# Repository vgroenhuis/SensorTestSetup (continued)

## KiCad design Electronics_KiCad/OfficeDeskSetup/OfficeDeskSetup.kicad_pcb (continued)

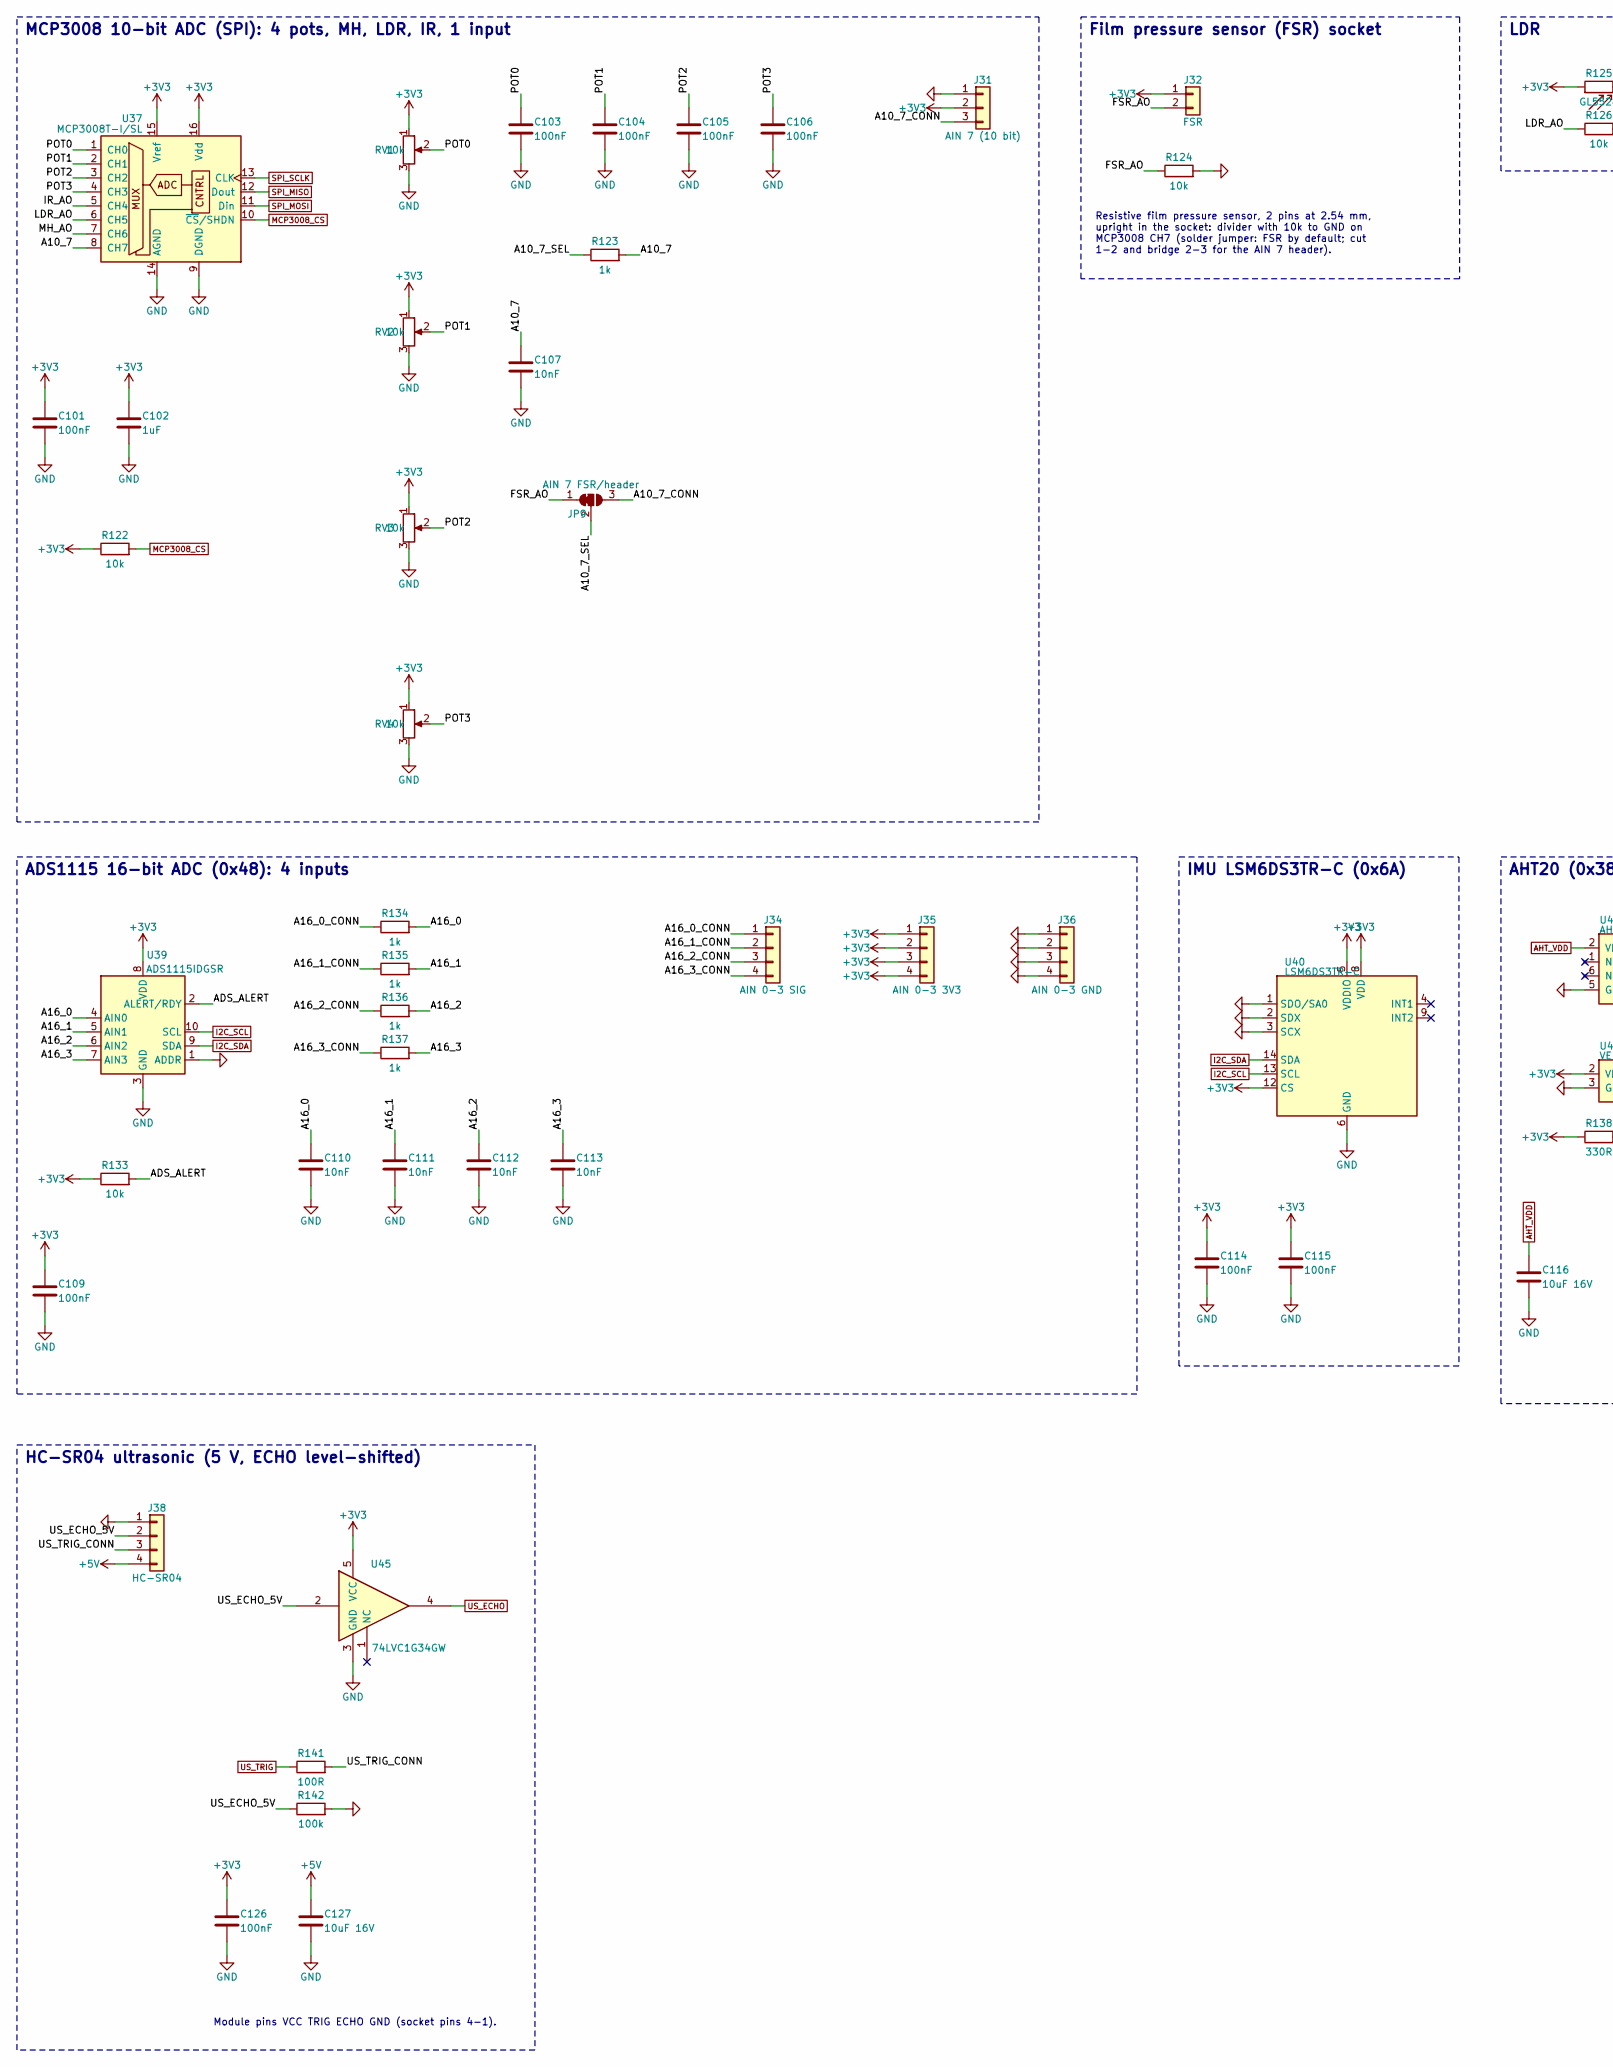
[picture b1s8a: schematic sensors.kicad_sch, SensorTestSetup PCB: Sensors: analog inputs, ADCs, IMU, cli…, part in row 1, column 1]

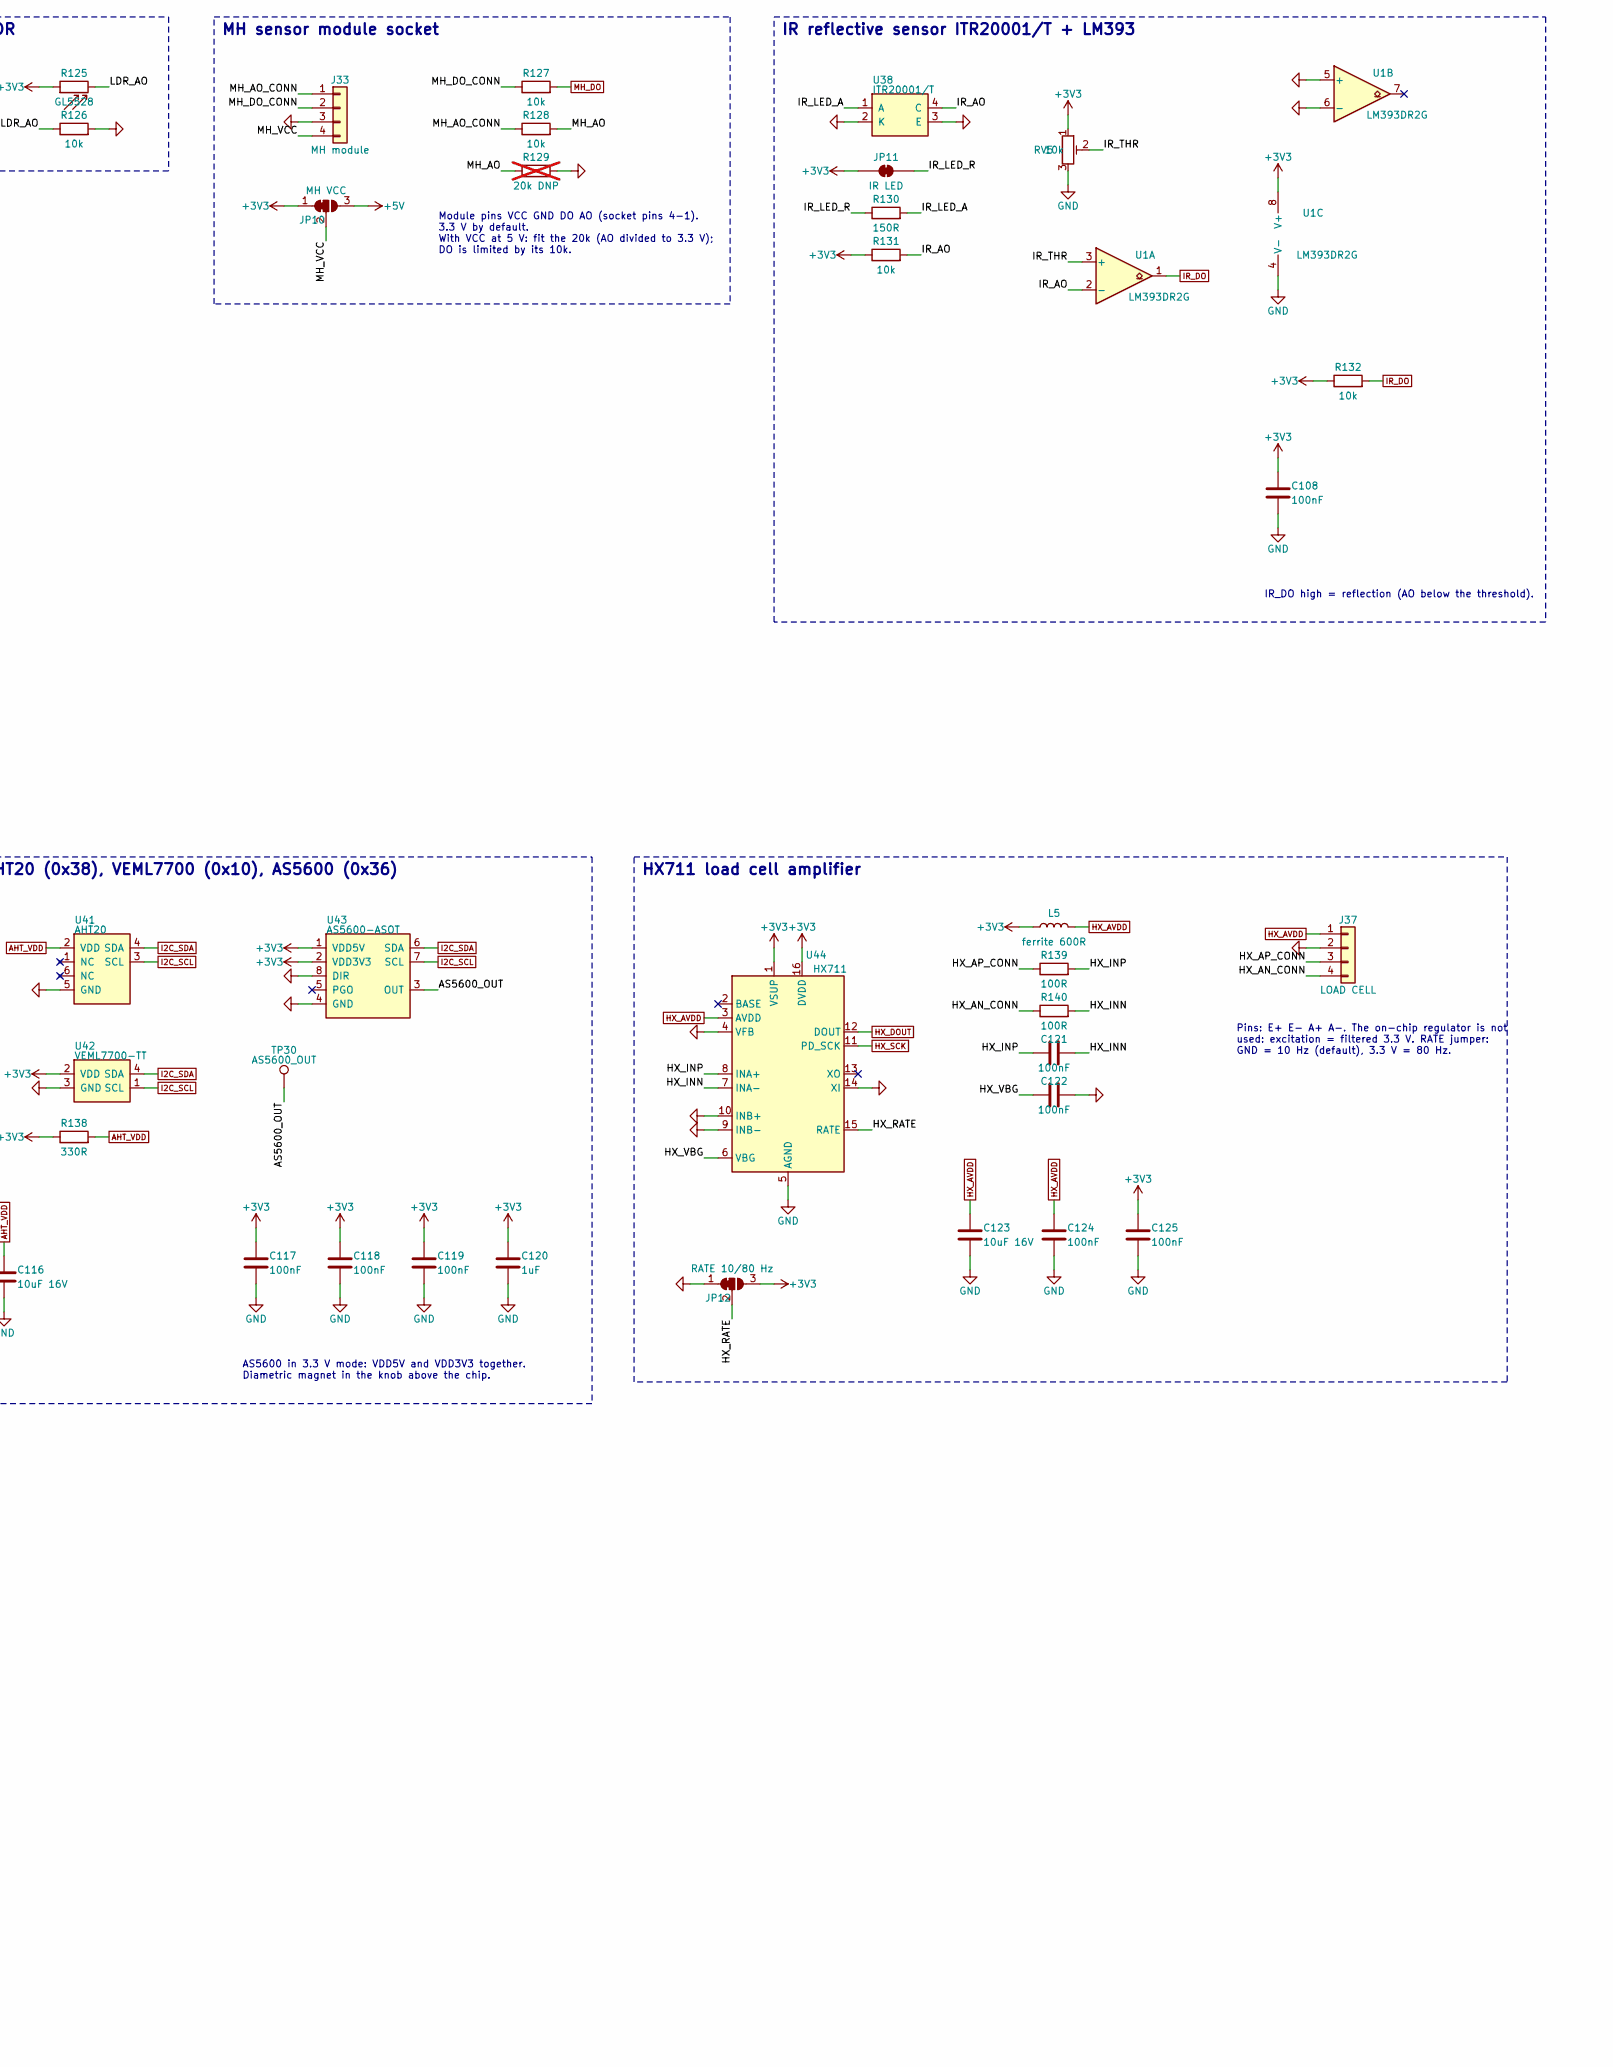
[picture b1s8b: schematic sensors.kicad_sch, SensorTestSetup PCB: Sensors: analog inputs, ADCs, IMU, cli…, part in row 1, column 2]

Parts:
C101, C103, C104, C105, C106, C108, C109, C114, C115, C117, C118, C119, C121, C122, C124, C125, C126: 100nF; C_0603_1608Metric; LCSC C14663
C102, C120: 1uF; C_0603_1608Metric; LCSC C15849
C107, C110, C111, C112, C113: 10nF; C_0603_1608Metric; LCSC C57112
C116, C123, C127: 10uF 16V; C_0805_2012Metric; LCSC C15850
J31: AIN 7 (10 bit); PinHeader_1x03_P2.54mm_Vertical; LCSC C49257
J32: FSR; PinSocket_1x02_P2.54mm_Vertical
J33: MH module; PinSocket_1x04_P2.54mm_Vertical; LCSC C2718488
J34: AIN 0-3 SIG; PinHeader_1x04_P2.54mm_Vertical; LCSC C42431808
J35: AIN 0-3 3V3; PinHeader_1x04_P2.54mm_Vertical; LCSC C42431808
J36: AIN 0-3 GND; PinHeader_1x04_P2.54mm_Vertical; LCSC C42431808
J37: LOAD CELL; JST_PH_B4B-PH-K_1x04_P2.00mm_Vertical; LCSC C131334
J38: HC-SR04; PinSocket_1x04_P2.54mm_Vertical; LCSC C2718488
JP9: AIN 7 FSR/header; SolderJumper-3_P1.3mm_Bridged12_RoundedPad1.0x1.5mm
JP10: MH VCC; SolderJumper-3_P1.3mm_Bridged12_RoundedPad1.0x1.5mm
JP11: IR LED; SolderJumper-2_P1.3mm_Bridged_RoundedPad1.0x1.5mm
JP12: RATE 10/80 Hz; SolderJumper-3_P1.3mm_Bridged12_RoundedPad1.0x1.5mm
L5: ferrite 600R; R_0603_1608Metric; LCSC C1002
R122, R124, R126, R127, R128, R131, R132, R133: 10k; R_0603_1608Metric; LCSC C25804
R123, R134, R135, R136, R137: 1k; R_0603_1608Metric; LCSC C21190
R125: GL5528; R_LDR_5.1x4.3mm_P3.4mm_Vertical; LCSC C125627
R129: 20k DNP; R_0603_1608Metric; LCSC C4184; not fitted
R130: 150R; R_0603_1608Metric; LCSC C22808
R138: 330R; R_0603_1608Metric; LCSC C23138
R139, R140, R141: 100R; R_0603_1608Metric; LCSC C22775
R142: 100k; R_0603_1608Metric; LCSC C25803
RV1, RV2, RV3, RV4: 10k; Potentiometer_Alps_RK09K_Single_Vertical; LCSC C209770
RV5: 10k; Potentiometer_Bourns_3314G_Vertical; LCSC C780220
TP30: AS5600_OUT; TestPoint_Pad_D1.5mm
U1: LM393DR2G; SOIC-8_3.9x4.9mm_P1.27mm; LCSC C7955
U37: MCP3008T-I/SL; SOIC-16_3.9x9.9mm_P1.27mm; LCSC C2651321
U38: ITR20001/T; OPTO-TH_4P_ITR20001-T-F316; LCSC C264269
U39: ADS1115IDGSR; TSSOP-10_3x3mm_P0.5mm; LCSC C37593
U40: LSM6DS3TR-C; LGA-14_3x2.5mm_P0.5mm_LayoutBorder3x4y; LCSC C967633
U41: AHT20; SENSOR-SMD_L3.0-W3.0-P1.00-BR; LCSC C2757850
U42: VEML7700-TT; SENSOR-SMD_EML7700-TT; LCSC C1850416
U43: AS5600-ASOT; SOIC-8_3.9x4.9mm_P1.27mm; LCSC C55240803
U44: HX711; SOIC-16_3.9x9.9mm_P1.27mm; LCSC C6705483
U45: 74LVC1G34GW; SOT-353_SC-70-5; LCSC C52140426

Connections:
+3V3: C101.1, C102.1, C108.1, C109.1, C114.1, C115.1, C117.1, C118.1, C119.1, C120.1, C125.1, C126.1, J31.2, J32.1, J35.1, J35.2, J35.3, J35.4, JP10.1 (A), JP11.1 (A), JP12.3 (B), L5.1, R122.1, R125.1, R131.1, R132.1, R133.1, R138.1, RV1.1, RV2.1, RV3.1, RV4.1, RV5.1, U1.8 (V+), U37.15 (Vref), U37.16 (Vdd), U39.8 (VDD), U40.5 (VDDIO), U40.8 (VDD), U40.12 (CS), U42.2 (VDD), U43.1 (VDD5V), U43.2 (VDD3V3), U44.1 (VSUP), U44.16 (DVDD), U45.5 (VCC); also elsewhere on the board
+5V: C127.1, J38.4, JP10.3 (B); also elsewhere on the board
/7 Sensors: analog inputs, ADCs, IMU, climate, light, angle, load cell, ultraso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: C107.1, R123.2, U37.8 (CH7)
/7 Sensors: analog inputs, ADCs, IMU, climate, light, angle, load cell, ultraso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: J31.3, JP9.3 (B)
/7 Sensors: analog inputs, ADCs, IMU, climate, light, angle, load cell, ultraso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: JP9.2 (C), R123.1
/7 Sensors: analog inputs, ADCs, IMU, climate, light, angle, load cell, ultraso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: C110.1, R134.2, U39.4 (AIN0)
/7 Sensors: analog inputs, ADCs, IMU, climate, light, angle, load cell, ultraso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: J34.1, R134.1
/7 Sensors: analog inputs, ADCs, IMU, climate, light, angle, load cell, ultraso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: C111.1, R135.2, U39.5 (AIN1)
/7 Sensors: analog inputs, ADCs, IMU, climate, light, angle, load cell, ultraso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: J34.2, R135.1
/7 Sensors: analog inputs, ADCs, IMU, climate, light, angle, load cell, ultraso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: C112.1, R136.2, U39.6 (AIN2)
/7 Sensors: analog inputs, ADCs, IMU, climate, light, angle, load cell, ultraso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: J34.3, R136.1
/7 Sensors: analog inputs, ADCs, IMU, climate, light, angle, load cell, ultraso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: C113.1, R137.2, U39.7 (AIN3)
/7 Sensors: analog inputs, ADCs, IMU, climate, light, angle, load cell, ultraso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: J34.4, R137.1
/7 Sensors: analog inputs, ADCs, IMU, climate, light, angle, load cell, ultraso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: R133.2, U39.2 (ALERT/RDY)
/7 Sensors: analog inputs, ADCs, IMU, climate, light, angle, load cell, ultraso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: TP30.1, U43.3 (OUT)
/7 Sensors: analog inputs, ADCs, IMU, climate, light, angle, load cell, ultraso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: J32.2, JP9.1 (A), R124.1
/7 Sensors: analog inputs, ADCs, IMU, climate, light, angle, load cell, ultraso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: J37.4, R140.1
/7 Sensors: analog inputs, ADCs, IMU, climate, light, angle, load cell, ultraso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: J37.3, R139.1
/7 Sensors: analog inputs, ADCs, IMU, climate, light, angle, load cell, ultraso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: C121.2, R140.2, U44.7 (INA-)
/7 Sensors: analog inputs, ADCs, IMU, climate, light, angle, load cell, ultraso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: C121.1, R139.2, U44.8 (INA+)
/7 Sensors: analog inputs, ADCs, IMU, climate, light, angle, load cell, ultraso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: JP12.2 (C), U44.15 (RATE)
/7 Sensors: analog inputs, ADCs, IMU, climate, light, angle, load cell, ultraso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: C122.1, U44.6 (VBG)
/7 Sensors: analog inputs, ADCs, IMU, climate, light, angle, load cell, ultraso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: R131.2, U1.2 (-), U37.5 (CH4), U38.4 (C)
/7 Sensors: analog inputs, ADCs, IMU, climate, light, angle, load cell, ultraso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: R130.2, U38.1 (A)
/7 Sensors: analog inputs, ADCs, IMU, climate, light, angle, load cell, ultraso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: JP11.2 (B), R130.1
/7 Sensors: analog inputs, ADCs, IMU, climate, light, angle, load cell, ultraso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: RV5.2, U1.3 (+)
/7 Sensors: analog inputs, ADCs, IMU, climate, light, angle, load cell, ultraso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: R125.2, R126.1, U37.6 (CH5)
/7 Sensors: analog inputs, ADCs, IMU, climate, light, angle, load cell, ultraso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: R128.2, R129.1, U37.7 (CH6)
/7 Sensors: analog inputs, ADCs, IMU, climate, light, angle, load cell, ultraso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: J33.1, R128.1
/7 Sensors: analog inputs, ADCs, IMU, climate, light, angle, load cell, ultraso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: J33.2, R127.1
/7 Sensors: analog inputs, ADCs, IMU, climate, light, angle, load cell, ultraso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: J33.4, JP10.2 (C)
/7 Sensors: analog inputs, ADCs, IMU, climate, light, angle, load cell, ultraso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: C103.1, RV1.2, U37.1 (CH0)
/7 Sensors: analog inputs, ADCs, IMU, climate, light, angle, load cell, ultraso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: C104.1, RV2.2, U37.2 (CH1)
/7 Sensors: analog inputs, ADCs, IMU, climate, light, angle, load cell, ultraso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: C105.1, RV3.2, U37.3 (CH2)
/7 Sensors: analog inputs, ADCs, IMU, climate, light, angle, load cell, ultraso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: C106.1, RV4.2, U37.4 (CH3)
/7 Sensors: analog inputs, ADCs, IMU, climate, light, angle, load cell, ultraso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: J38.2, R142.1, U45.2
/7 Sensors: analog inputs, ADCs, IMU, climate, light, angle, load cell, ultraso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: J38.3, R141.2
AHT_VDD: C116.1, R138.2, U41.2 (VDD)
GND: C101.2, C102.2, C103.2, C104.2, C105.2, C106.2, C107.2, C108.2, C109.2, C110.2, C111.2, C112.2, C113.2, C114.2, C115.2, C116.2, C117.2, C118.2, C119.2, C120.2, C122.2, C123.2, C124.2, C125.2, C126.2, C127.2, J31.1, J33.3, J36.1, J36.2, J36.3, J36.4, J37.2, J38.1, JP12.1 (A), R124.2, R126.2, R129.2, R142.2, RV1.3, RV2.3, RV3.3, RV4.3, RV5.3, U1.4 (V-), U1.5 (+), U1.6 (-), U37.9 (DGND), U37.14 (AGND), U38.2 (K), U38.3 (E), U39.1 (ADDR), U39.3 (GND), U40.1 (SDO/SA0), U40.2 (SDX), U40.3 (SCX), U40.6 (GND), U40.7 (GND), U41.5 (GND), U42.3 (GND), U43.4 (GND), U43.8 (DIR), U44.4 (VFB), U44.5 (AGND), U44.9 (INB-), U44.10 (INB+), U44.14 (XI), U45.3 (GND); also elsewhere on the board
HX_AVDD: C123.1, C124.1, J37.1, L5.2, U44.3 (AVDD)
HX_DOUT: U44.12 (DOUT); also elsewhere on the board
HX_SCK: U44.11 (PD_SCK); also elsewhere on the board
I2C_SCL: U39.10 (SCL), U40.13 (SCL), U41.3 (SCL), U42.1 (SCL), U43.7 (SCL); also elsewhere on the board
I2C_SDA: U39.9 (SDA), U40.14 (SDA), U41.4 (SDA), U42.4 (SDA), U43.6 (SDA); also elsewhere on the board
IR_DO: R132.2, U1.1; also elsewhere on the board
MCP3008_CS: R122.2, U37.10 (~CS/SHDN); also elsewhere on the board
MH_DO: R127.2; also elsewhere on the board
SPI_MISO: U37.12 (Dout); also elsewhere on the board
SPI_MOSI: U37.11 (Din); also elsewhere on the board
SPI_SCLK: U37.13 (CLK); also elsewhere on the board
US_ECHO: U45.4; also elsewhere on the board
US_TRIG: R141.1; also elsewhere on the board

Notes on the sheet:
MCP3008 10-bit ADC (SPI): 4 pots, MH, LDR, IR, 1 input
Resistive film pressure sensor, 2 pins at 2.54 mm, upright in the socket: divider with 10k to GND on MCP3008 CH7 (solder jumper: FSR by default; cut 1-2 and bridge 2-3 for the AIN 7 header).
Film pressure sensor (FSR) socket
LDR
Module pins VCC GND DO AO (socket pins 4-1). 3.3 V by default. With VCC at 5 V: fit the 20k (AO divided to 3.3 V); DO is limited by its 10k.
MH sensor module socket
IR_DO high = reflection (AO below the threshold).
IR reflective sensor ITR20001/T + LM393
ADS1115 16-bit ADC (0x48): 4 inputs
IMU LSM6DS3TR-C (0x6A)
AS5600 in 3.3 V mode: VDD5V and VDD3V3 together. Diametric magnet in the knob above the chip.
AHT20 (0x38), VEML7700 (0x10), AS5600 (0x36)
Pins: E+ E- A+ A-. The on-chip regulator is not used: excitation = filtered 3.3 V. RATE jumper: GND = 10 Hz (default), 3.3 V = 80 Hz.
HX711 load cell amplifier
Module pins VCC TRIG ECHO GND (socket pins 4-1).
HC-SR04 ultrasonic (5 V, ECHO level-shifted)

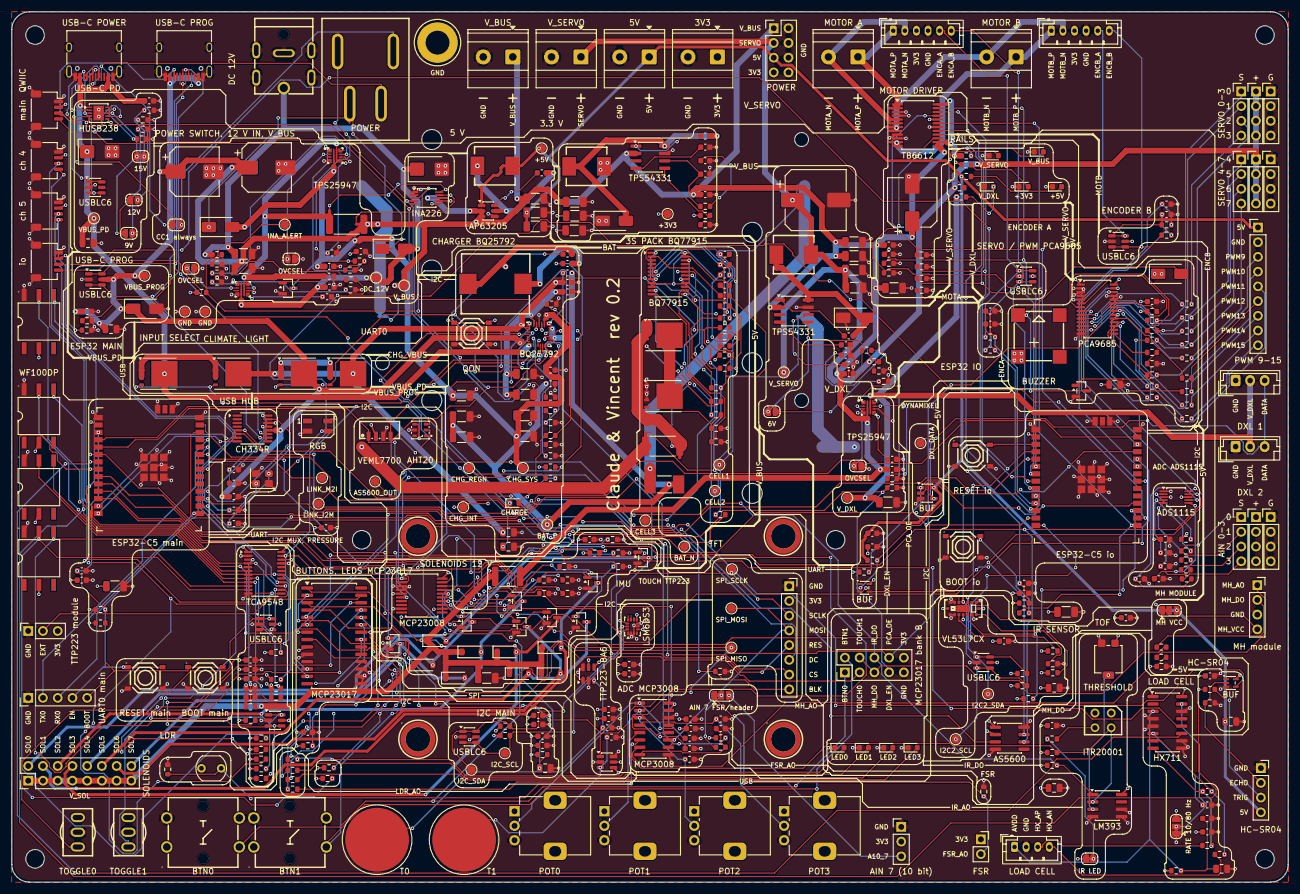
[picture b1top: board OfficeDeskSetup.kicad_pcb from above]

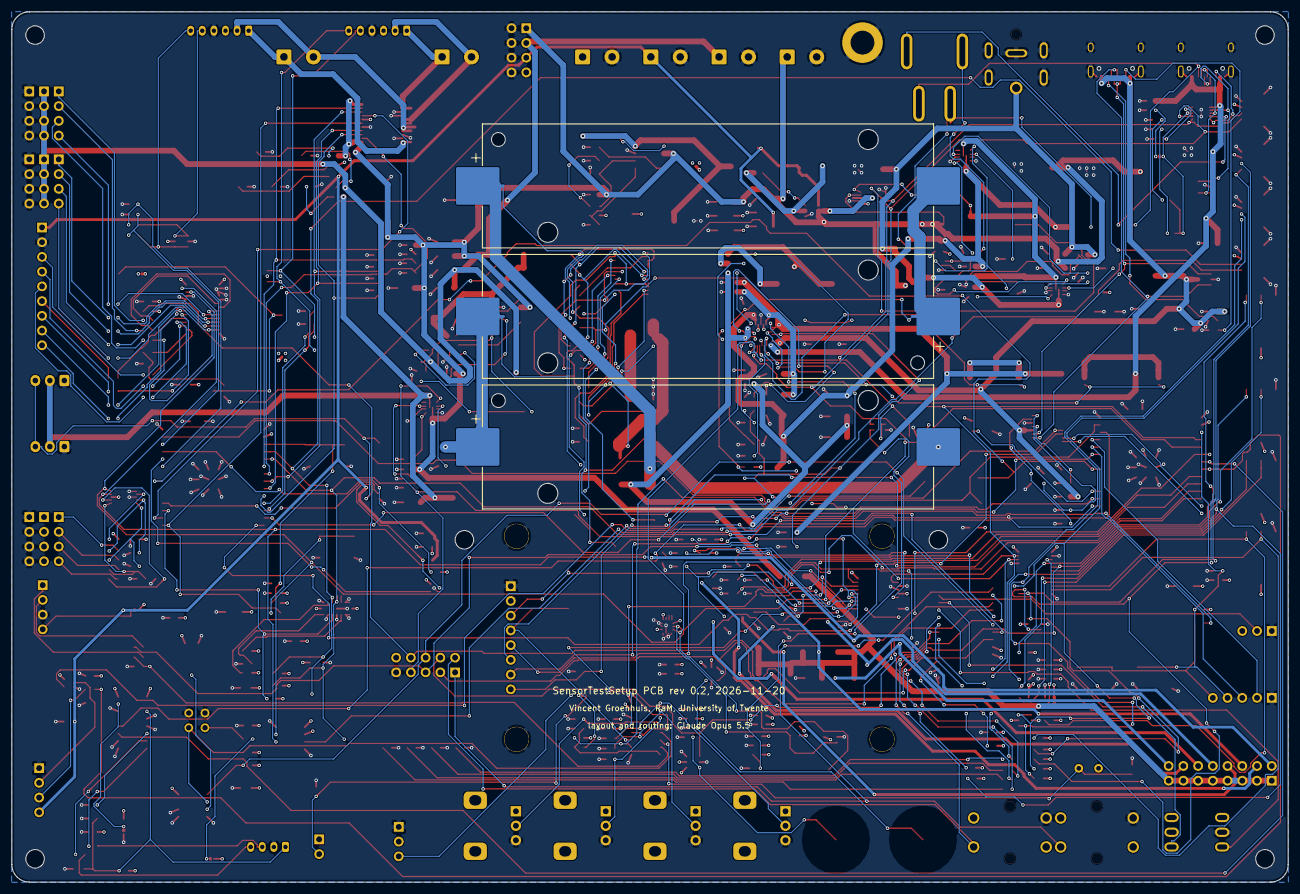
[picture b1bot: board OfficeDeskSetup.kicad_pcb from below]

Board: 4 copper layers, 220.0 x 150.0 mm, 486 parts (6 on the bottom side), 291 nets.

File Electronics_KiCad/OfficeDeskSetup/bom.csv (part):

Reference,Value,Footprint,LCSC,DNP,Sheet,Note
J1,USB-C POWER,Connector_USB:USB_C_Receptacle_HRO_TYPE-C-31-M-12,C165948,,usb_pd,
U2,HUSB238_002DD,Package_DFN_QFN:WDFN-10-1EP_3x3mm_P0.5mm_EP1.8x2.5mm,C7471904,,usb_pd,
U3,USBLC6-2SC6,Package_TO_SOT_SMD:SOT-23-6,C2827654,,usb_pd,
JP1,15V,Jumper:SolderJumper-2_P1.3mm_Bridged_RoundedPad1.0x1.5mm,,,usb_pd,
R1,14k,Resistor_SMD:R_0603_1608Metric,C22803,,usb_pd,
JP2,12V,Jumper:SolderJumper-2_P1.3mm_Open_RoundedPad1.0x1.5mm,,,usb_pd,
R2,10k,Resistor_SMD:R_0603_1608Metric,C25804,,usb_pd,
JP3,9V,Jumper:SolderJumper-2_P1.3mm_Open_RoundedPad1.0x1.5mm,,,usb_pd,
R3,6.04k,Resistor_SMD:R_0603_1608Metric,C25977,,usb_pd,
R4,ISET DNP,Resistor_SMD:R_0603_1608Metric,,DNP,usb_pd,
D1,SMBJ22A,Diode_SMD:D_SMB,C10214,,usb_pd,
C1,1uF 35V,Capacitor_SMD:C_0805_2012Metric,C28323,,usb_pd,
C2,100nF 50V,Capacitor_SMD:C_0603_1608Metric,C14663,,usb_pd,
TP1,VBUS_PD,TestPoint:TestPoint_Pad_D1.5mm,,,usb_pd,
J2,USB-C PROG,Connector_USB:USB_C_Receptacle_HRO_TYPE-C-31-M-12,C165948,,usb_pd,
R5,5.1k,Resistor_SMD:R_0603_1608Metric,C23186,,usb_pd,
R6,5.1k,Resistor_SMD:R_0603_1608Metric,C23186,,usb_pd,
D2,SMAJ5.0A,Diode_SMD:D_SMA,C19077523,,usb_pd,
U4,USBLC6-2SC6,Package_TO_SOT_SMD:SOT-23-6,C2827654,,usb_pd,
C3,10uF 16V,Capacitor_SMD:C_0805_2012Metric,C15850,,usb_pd,
C4,100nF,Capacitor_SMD:C_0603_1608Metric,C14663,,usb_pd,
TP2,VBUS_PROG,TestPoint:TestPoint_Pad_D1.5mm,,,usb_pd,
U5,CH334R,Package_SO:QSOP-16_3.9x4.9mm_P0.635mm,C4154405,,usb_pd,
Y1,12MHz,Crystal:Crystal_SMD_3225-4Pin_3.2x2.5mm,C9002,,usb_pd,
C5,100nF,Capacitor_SMD:C_0603_1608Metric,C14663,,usb_pd,
C6,1uF,Capacitor_SMD:C_0603_1608Metric,C15849,,usb_pd,
C7,100nF,Capacitor_SMD:C_0603_1608Metric,C14663,,usb_pd,
C8,15pF DNP,Capacitor_SMD:C_0603_1608Metric,C1644,DNP,usb_pd,
C9,15pF DNP,Capacitor_SMD:C_0603_1608Metric,C1644,DNP,usb_pd,
Q1,BSC0902NSI,Package_TO_SOT_SMD:TDSON-8-1,C534382,,battery,ACFET1: drain to the input
Q2,BSC0902NSI,Package_TO_SOT_SMD:TDSON-8-1,C534382,,battery,RBFET1: drain to the charger VBUS
Q3,BSC0902NSI,Package_TO_SOT_SMD:TDSON-8-1,C534382,,battery,ACFET2: drain to the input
Q4,BSC0902NSI,Package_TO_SOT_SMD:TDSON-8-1,C534382,,battery,RBFET2: drain to the charger VBUS
U6,BQ25792RQMR,Package_DFN_QFN:Texas_RQM0029A_VQFN-29_4x4mm_P0.4mm,C2862876,,battery,
L1,2.2uH 10A,OfficeDeskSetup:IND-SMD_L11.5-W10.5,C167228,,battery,
C10,47nF 50V,Capacitor_SMD:C_0603_1608Metric,C1622,,battery,
C11,47nF 50V,Capacitor_SMD:C_0603_1608Metric,C1622,,battery,
C12,1nF 50V,Capacitor_SMD:C_0603_1608Metric,C1588,,battery,
R7,13.7k,Resistor_SMD:R_0603_1608Metric,C22793,,battery,
R8,47k,Resistor_SMD:R_0603_1608Metric,C25819,,battery,
R9,100k,Resistor_SMD:R_0603_1608Metric,C25803,,battery,
R10,5.23k,Resistor_SMD:R_0603_1608Metric,C23068,,battery,
R11,30.1k,Resistor_SMD:R_0603_1608Metric,C23000,,battery,
TH1,10k B3435,Resistor_SMD:R_0603_1608Metric,C525660,,battery,
R12,10k,Resistor_SMD:R_0603_1608Metric,C25804,,battery,
R13,10k,Resistor_SMD:R_0603_1608Metric,C25804,,battery,
R14,2.2k,Resistor_SMD:R_0603_1608Metric,C4190,,battery,
D3,CHARGE yellow,LED_SMD:LED_0603_1608Metric,C2287,,battery,
SW1,QON,OfficeDeskSetup:SW-SMD_4P-L5.1-W5.1-P3.70-LS6.5-TL_H1.5,C318884,,battery,
C13,4.7uF 35V,Capacitor_SMD:C_0805_2012Metric,C76651,,battery,
C14,100nF 50V,Capacitor_SMD:C_0603_1608Metric,C14663,,battery,
C15,10uF 35V,Capacitor_SMD:C_1206_3216Metric,C13585,,battery,
C16,10uF 35V,Capacitor_SMD:C_1206_3216Metric,C13585,,battery,
C17,100nF 50V,Capacitor_SMD:C_0603_1608Metric,C14663,,battery,
C18,4.7uF 16V,Capacitor_SMD:C_0805_2012Metric,C1779,,battery,
C19,22uF 25V,Capacitor_SMD:C_1206_3216Metric,C12891,,battery,
C20,22uF 25V,Capacitor_SMD:C_1206_3216Metric,C12891,,battery,
C21,22uF 25V,Capacitor_SMD:C_1206_3216Metric,C12891,,battery,
C22,100nF 50V,Capacitor_SMD:C_0603_1608Metric,C14663,,battery,
C23,10uF 25V,Capacitor_SMD:C_1206_3216Metric,C13585,,battery,
C24,10uF 25V,Capacitor_SMD:C_1206_3216Metric,C13585,,battery,
C25,100nF 50V,Capacitor_SMD:C_0603_1608Metric,C14663,,battery,
TP3,CHG_SYS,TestPoint:TestPoint_Pad_D1.5mm,,,battery,
TP4,BAT_P,TestPoint:TestPoint_Pad_D1.5mm,,,battery,
TP5,CHG_INT,TestPoint:TestPoint_Pad_D1.5mm,,,battery,
TP6,CHG_REGN,TestPoint:TestPoint_Pad_D1.5mm,,,battery,
BT1,18650,Battery:BatteryHolder_Keystone_1042_1x18650,C2979183,,battery,holder MY-18650-01: footprint to check
BT2,18650,Battery:BatteryHolder_Keystone_1042_1x18650,C2979183,,battery,holder MY-18650-01: footprint to check
BT3,18650,Battery:BatteryHolder_Keystone_1042_1x18650,C2979183,,battery,holder MY-18650-01: footprint to check
F1,10A,Fuse:Fuse_Littelfuse-NANO2-451_453,C44479,,battery,
NT1,CELL1 tap,NetTie:NetTie-2_SMD_Pad0.5mm,,,battery,
NT2,CELL2 tap,NetTie:NetTie-2_SMD_Pad0.5mm,,,battery,
NT3,CELL3 tap,NetTie:NetTie-2_SMD_Pad0.5mm,,,battery,
NT4,Kelvin BAT-,NetTie:NetTie-2_SMD_Pad0.5mm,,,battery,
NT5,Kelvin SRN,NetTie:NetTie-2_SMD_Pad0.5mm,,,battery,
U7,BQ7791504PWR,Package_SO:TSSOP-24_4.4x7.8mm_P0.65mm,C2873309,,battery,
R15,1k,Resistor_SMD:R_0603_1608Metric,C21190,,battery,
R16,100R,Resistor_SMD:R_0603_1608Metric,C22775,,battery,
R17,100R,Resistor_SMD:R_0603_1608Metric,C22775,,battery,
R18,100R,Resistor_SMD:R_0603_1608Metric,C22775,,battery,
R19,100R,Resistor_SMD:R_0603_1608Metric,C22775,,battery,
C26,100nF,Capacitor_SMD:C_0603_1608Metric,C14663,,battery,
C27,100nF,Capacitor_SMD:C_0603_1608Metric,C14663,,battery,
C28,100nF,Capacitor_SMD:C_0603_1608Metric,C14663,,battery,
C29,1uF 25V,Capacitor_SMD:C_0603_1608Metric,C15849,,battery,
C30,1uF,Capacitor_SMD:C_0603_1608Metric,C15849,,battery,
R20,10k,Resistor_SMD:R_0603_1608Metric,C25804,,battery,
TH2,10k B3435,Resistor_SMD:R_0603_1608Metric,C525660,,battery,
R21,100k,Resistor_SMD:R_0603_1608Metric,C25803,,battery,
R22,100k,Resistor_SMD:R_0603_1608Metric,C25803,,battery,
R23,5mR 1W,Resistor_SMD:R_2512_6332Metric,C393074,,battery,
Q5,BSC0902NSI,Package_TO_SOT_SMD:TDSON-8-1,C534382,,battery,discharge FET
Q6,BSC0902NSI,Package_TO_SOT_SMD:TDSON-8-1,C534382,,battery,charge FET
R24,4.53k,Resistor_SMD:R_0603_1608Metric,C25971,,battery,
R25,1M,Resistor_SMD:R_0603_1608Metric,C22935,,battery,
R26,3.3M,Resistor_SMD:R_0603_1608Metric,C26096,,battery,
R27,453k,Resistor_SMD:R_0603_1608Metric,C25818,,battery,
TP7,CELL1,TestPoint:TestPoint_Pad_D1.5mm,,,battery,
TP8,CELL2,TestPoint:TestPoint_Pad_D1.5mm,,,battery,
TP9,CELL3,TestPoint:TestPoint_Pad_D1.5mm,,,battery,
TP10,BAT_N,TestPoint:TestPoint_Pad_D1.5mm,,,battery,
SW2,POWER,OfficeDeskSetup:SW-TH_SS21-BBIWG2-B,C6775929,,rails,
JP4,CC1 always,Jumper:SolderJumper-2_P1.3mm_Open_RoundedPad1.0x1.5mm,,,rails,
D4,SS14,Diode_SMD:D_SMA,C2480,,rails,
D5,SS14,Diode_SMD:D_SMA,C2480,,rails,
R28,1M,Resistor_SMD:R_0603_1608Metric,C22935,,rails,
R29,169k,Resistor_SMD:R_0603_1608Metric,C22817,,rails,
R30,1M,Resistor_SMD:R_0603_1608Metric,C22935,,rails,
R31,169k,Resistor_SMD:R_0603_1608Metric,C22817,,rails,
Q7,AO3400A,Package_TO_SOT_SMD:SOT-23,C20917,,rails,
R32,100k,Resistor_SMD:R_0603_1608Metric,C25803,,rails,
R33,100k,Resistor_SMD:R_0603_1608Metric,C25803,,rails,
U8,TPS259472ARPWR,OfficeDeskSetup:VQFN-10_L2.0-W2.0-P0.45-TL,C3662789,,rails,
R34,665R,Resistor_SMD:R_0603_1608Metric,C218112,,rails,
C31,10nF,Capacitor_SMD:C_0603_1608Metric,C57112,,rails,
JP5,OVCSEL,Jumper:SolderJumper-2_P1.3mm_Open_RoundedPad1.0x1.5mm,,,rails,
C32,1uF 25V,Capacitor_SMD:C_0603_1608Metric,C15849,,rails,
C33,1uF 25V,Capacitor_SMD:C_0603_1608Metric,C15849,,rails,
J3,DC 12V,OfficeDeskSetup:DC-IN-TH_HX-DC007B-2.5,C17701683,,rails,
D6,SMBJ15A,Diode_SMD:D_SMB,C435932,,rails,
C34,10uF 25V,Capacitor_SMD:C_1206_3216Metric,C13585,,rails,
C35,1uF 25V,Capacitor_SMD:C_0603_1608Metric,C15849,,rails,
TP11,DC_12V,TestPoint:TestPoint_Pad_D1.5mm,,,rails,
U9,TPS259472ARPWR,OfficeDeskSetup:VQFN-10_L2.0-W2.0-P0.45-TL,C3662789,,rails,
R35,665R,Resistor_SMD:R_0603_1608Metric,C218112,,rails,
C36,10nF,Capacitor_SMD:C_0603_1608Metric,C57112,,rails,
JP6,OVCSEL,Jumper:SolderJumper-2_P1.3mm_Open_RoundedPad1.0x1.5mm,,,rails,
R36,10mR 2W,Resistor_SMD:R_2512_6332Metric,C192580,,rails,
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
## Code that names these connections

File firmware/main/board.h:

// Pins of the breadboard setup (ESP32-C5-DevKitC-1 N16R8), as wired in the PlatformIO firmware
// (ESP32_C5_Breadboard_PlatformIO/src). Its README pinout table is older than the wiring in places.
#pragma once

// SPI bus: OLED display and MCP3008 A/D converter
#define PIN_SPI_SCLK        7
#define PIN_SPI_MOSI        8
#define PIN_SPI_MISO        0
#define PIN_OLED_CS         25
#define PIN_OLED_DC         9
#define PIN_MCP3008_CS      28

// I2C bus: MCP23017, PCA9685, TCA9548 (pressure sensors), VL53L7CX
#define PIN_I2C_SDA         2
#define PIN_I2C_SCL         3

// L298N motor driver and the motor's encoder
#define PIN_MOTOR_IN1       24
#define PIN_MOTOR_IN2       23
#define PIN_ENC_A           26
#define PIN_ENC_B           4

// HC-SR04 ultrasonic sensor
#define PIN_US_TRIG         6
#define PIN_US_ECHO         10

// HX711 load cell amplifier
#define PIN_HX711_DOUT      5
#define PIN_HX711_SCK       1

// MCP3008 channels
#define MCP3008_CH_MH       6       // MH sensor module (analog out)
#define MCP3008_CH_POT      7       // potentiometer
#define MCP3008_VREF        3.3f

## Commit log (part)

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2026-06-14 Potmeter working
2026-06-14 Many new features, including controlling motor using potmeter
2026-06-17 OLED working, displays IP
2026-06-17 small fix
2026-06-21 Rotary encoder functional, several improvements
2026-06-27 Pressure sensors added; digital I/O added; various improvements
2026-06-28 MH sensor implemented with web interface. ToF sensor partially implemented (to serial only, no interface yet)
2026-06-29 Web interface for ToF sensor implemented
2026-06-29 Made 3d view of ToF sensor
